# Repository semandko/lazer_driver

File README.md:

# lazer_driver
Electronic driver for semiconductor lazer with syncronization.

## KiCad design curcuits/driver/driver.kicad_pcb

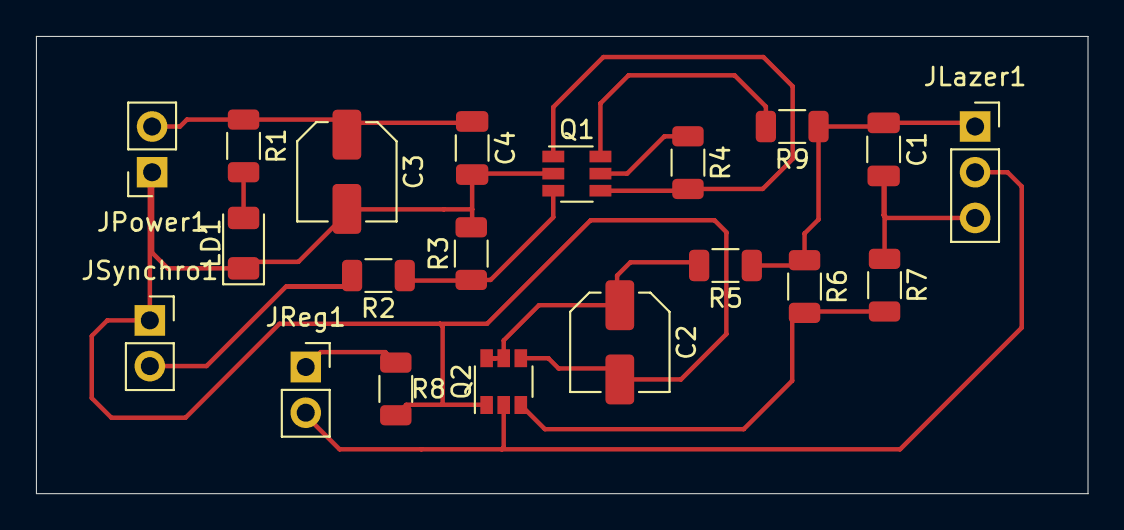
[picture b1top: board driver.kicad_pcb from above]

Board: 4 copper layers, 58.4 x 25.4 mm, 20 parts (0 on the bottom side), 12 nets.

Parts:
C1, C4: C100n; C_1206_3216Metric
C2, C3: CP10; C_Elec_5x5.8
JLazer1: Conn_01x03; PinSocket_1x03_P2.54mm_Vertical
JPower1: Conn_01x02; PinSocket_1x02_P2.54mm_Vertical
JReg1: Conn_01x02; PinSocket_1x02_P2.54mm_Vertical
JSynchro1: Conn_01x02; PinSocket_1x02_P2.54mm_Vertical
LD1: SFH4356P; LED_1206_3216Metric
Q1: DMC2053UVT; TSOT-23-6
Q2: BC846BDW1; SuperSOT-6
R1, R2: R_330; R_1206_3216Metric
R3: R_10K; R_1206_3216Metric
R4: R_1K; R_1206_3216Metric
R5: R1K; R_1206_3216Metric
R6: R10K; R_1206_3216Metric
R7: R50; R_1206_3216Metric
R8: R5K6; R_1206_3216Metric
R9: R000; R_1206_3216Metric

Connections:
GND: C2.2, C3.2, C4.2, JPower1.1, JSynchro1.1, LD1.1, Q1.2, Q2.1, Q2.4, R3.2, R8.2
unnamed: C1.1, JLazer1.1, Q1.6, R5.1, R6.1, R9.1, R9.2
unnamed: C1.2, JLazer1.3, R7.1
unnamed: C2.1, Q2.5, Q2.6, R5.2
unnamed: C3.1, C4.1, JPower1.2, Q1.5, R1.1, R4.1
unnamed: JReg1.1, R8.1
unnamed: JSynchro1.2, R2.2
unnamed: LD1.2, R1.2
unnamed: Q1.1, Q1.4, R4.2
unnamed: Q1.3, R2.1, R3.1
unnamed: Q2.3, R6.2, R7.2
PD: JLazer1.2, JReg1.2, Q2.2

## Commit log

2021-06-29 electronic shem was added
